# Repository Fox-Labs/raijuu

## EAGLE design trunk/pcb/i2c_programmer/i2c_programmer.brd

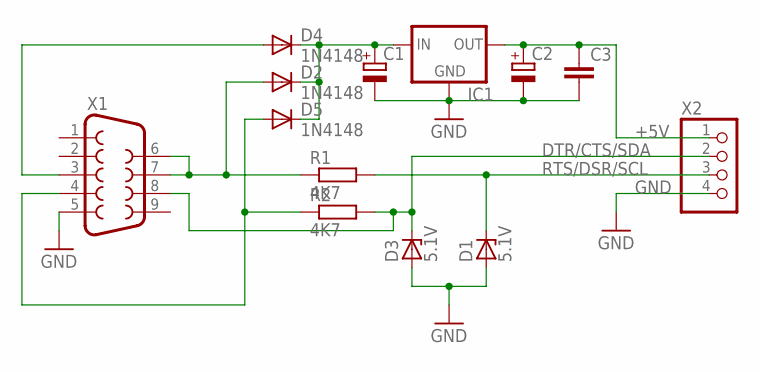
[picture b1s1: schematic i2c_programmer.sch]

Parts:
C1, C2: CPOL-EUE2.5-6; E2,5-6
C3: C-EU025-025X050; C025-025X050
D1, D3: 5.1V; DO41Z10
D2, D4, D5: 1N4148; DO41-10
IC1: 78LXX
R1, R2: 4K7; 0207/7
X1: F09HP
X2: 22-23-2041

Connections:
+5V: C2.+, C3.1, IC1.OUT, X2.1
DTR: D5.A, R2.1, X1.4
DTR/CTS/SDA: D3.C, R2.2, X1.8, X2.2
GND: C1.-, C2.-, C3.2, D1.A, D3.A, IC1.GND, X1.5, X2.4
unnamed: C1.+, D2.C, D4.C, D5.C, IC1.IN
RTS/DSR: D2.A, R1.1, X1.6, X1.7
RTS/DSR/SCL: D1.C, R1.2, X2.3
TXD: D4.A, X1.3

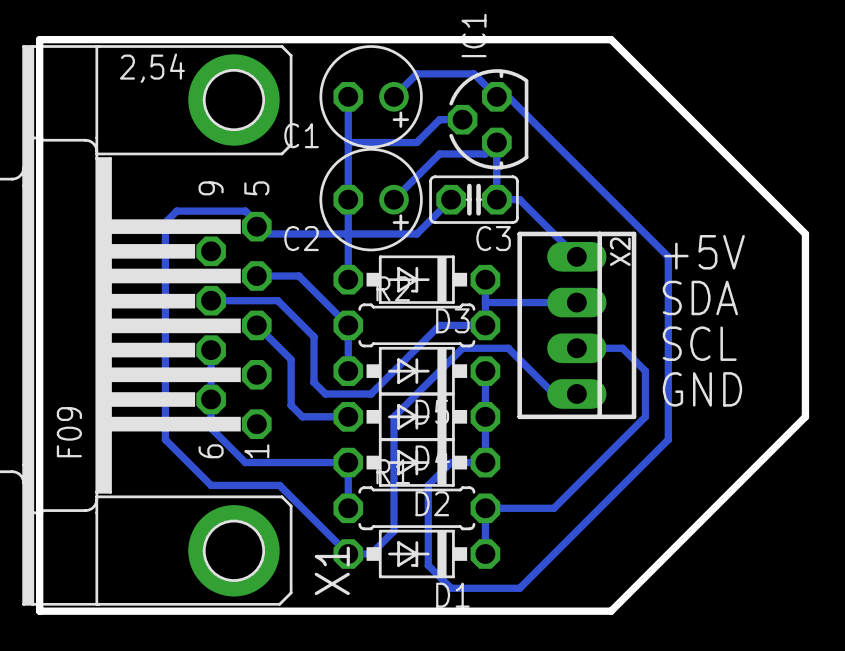
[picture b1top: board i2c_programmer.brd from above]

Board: 2 copper layers, 42.5 x 31.7 mm, 13 parts (0 on the bottom side), 8 nets.
